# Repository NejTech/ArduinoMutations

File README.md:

Arduino Mutations
============

Here is the resting place of various mutations of Arduino with different MCU's that
I made mostly in 2011 and I decided to release this to the world for reference.
All of the schematic and board designs in this repository are intended to be Open
Source Hardware (OSHW) and are licensed under the Modified BSD License. A short
readme is included in the <name>.txt files.

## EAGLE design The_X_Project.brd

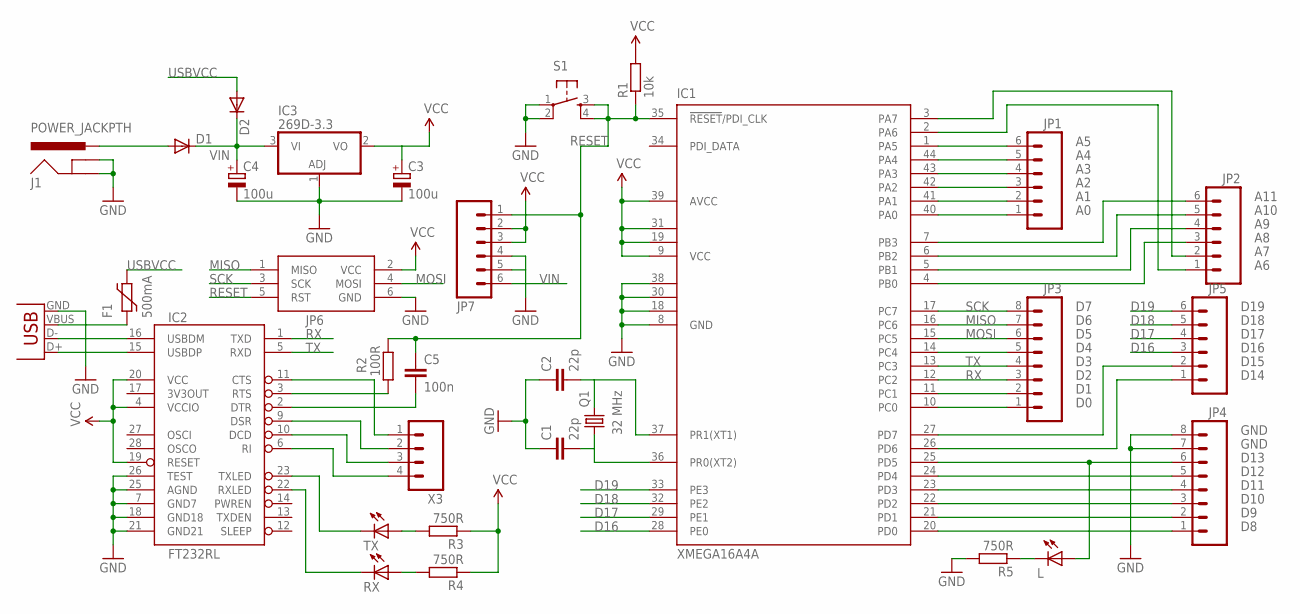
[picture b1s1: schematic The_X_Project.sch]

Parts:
C1, C2: 22p; C0805
C3, C4: 100u; PANASONIC_D
C5: 100n; C0805
D1, D2: DIODE-SMB; SMB
F1: 500mA; 1812L
IC1: XMEGA16A4A; TQFP44
IC2: FT232RL; SSOP28DB
IC3: 269D-3.3; DPACK
J1: POWER_JACKPTH; POWER_JACK_PTH
JP1, JP2, JP5, JP7: M06SIP; 1X06
JP3, JP4: M08; 1X08
JP6: AVRISP-6; AVRISP
L: LED1206; LED-1206
Q1: 32 MHz; HC49U-LM
R1: 10k; R0805
R2: 100R; R0805
R3, R4, R5: 750R; R0805
RX: LED1206; LED-1206
S1: TAC_SWITCHPTH; TACTILE-PTH
TX: LED1206; LED-1206
X1: USBSMD; USB-MINIB
X3: M04PTH; 1X04

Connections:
D16: IC1.28 (PE0), JP5.3
D17: IC1.29 (PE1), JP5.4
D18: IC1.32 (PE2), JP5.5
D19: IC1.33 (PE3), JP5.6
GND: C1.1, C2.1, C3.-, C4.-, IC1.8 (GND), IC1.18 (GND1), IC1.30 (GND2), IC1.38 (GND3), IC2.7 (GND7), IC2.18 (GND18), IC2.21 (GND21), IC2.25 (AGND), IC2.26 (TEST), IC3.1 (ADJ), J1.GND, J1.GNDBREAK, JP4.7, JP4.8, JP6.6 (GND), JP7.4, JP7.5, R5.2, S1.1, S1.2, X1.GND
MISO: IC1.16 (PC6), JP3.7, JP6.1 (MISO)
MOSI: IC1.15 (PC5), JP3.6, JP6.4 (MOSI)
unnamed: IC1.4 (PB0), JP2.3
unnamed: IC1.41 (PA1), JP1.2
unnamed: IC1.42 (PA2), JP1.3
unnamed: IC1.43 (PA3), JP1.4
unnamed: IC1.44 (PA4), JP1.5
unnamed: IC1.1 (PA5), JP1.6
unnamed: IC1.2 (PA6), JP2.1
unnamed: IC1.3 (PA7), JP2.2
unnamed: IC1.5 (PB1), JP2.4
unnamed: IC1.6 (PB2), JP2.5
unnamed: IC1.7 (PB3), JP2.6
unnamed: IC1.10 (PC0), JP3.1
unnamed: IC1.11 (PC1), JP3.2
unnamed: IC2.15 (USBDP), X1.D+
unnamed: IC2.16 (USBDM), X1.D-
unnamed: IC1.14 (PC4), JP3.5
unnamed: IC1.20 (PD0), JP4.1
unnamed: IC1.21 (PD1), JP4.2
unnamed: IC1.22 (PD2), JP4.3
unnamed: IC1.23 (PD3), JP4.4
unnamed: IC1.24 (PD4), JP4.5
unnamed: IC1.25 (PD5), JP4.6, L.A
unnamed: IC1.26 (PD6), JP5.1
unnamed: IC1.27 (PD7), JP5.2
unnamed: IC1.40 (PA0), JP1.1
unnamed: D1.A, J1.PWR
unnamed: F1.P$1 (1), X1.VBUS
unnamed: C1.2, IC1.36 (PR0(XT2)), Q1.1
unnamed: C2.2, IC1.37 (PR1(XT1)), Q1.2
unnamed: IC2.3 (RTS), R2.1
unnamed: C5.2, IC2.2 (DTR)
unnamed: IC2.6 (RI), X3.4
unnamed: IC2.10 (DCD), X3.3
unnamed: IC2.9 (DSR), X3.2
unnamed: IC2.11 (CTS), X3.1
unnamed: IC2.22 (RXLED), RX.C
unnamed: IC2.23 (TXLED), TX.C
unnamed: R4.2, RX.A
unnamed: R3.2, TX.A
unnamed: L.C, R5.1
RESET: C5.1, IC1.35 (!RESET!/PDI_CLK), JP6.5 (RST), JP7.1, R1.1, R2.2, S1.3, S1.4
RX: IC1.12 (PC2), IC2.1 (TXD), JP3.3
SCK: IC1.17 (PC7), JP3.8, JP6.3 (SCK)
TX: IC1.13 (PC3), IC2.5 (RXD), JP3.4
USBVCC: D2.A, F1.P$2 (2)
VCC: C3.+, IC1.9 (VCC), IC1.19 (VCC1), IC1.31 (VCC2), IC1.39 (AVCC), IC2.4 (VCCIO), IC2.19 (RESET), IC2.20 (VCC), IC3.2 (VO), JP6.2 (VCC), JP7.2, JP7.3, R1.2, R3.1, R4.1
VIN: C4.+, D1.C, D2.C, IC3.3 (VI), JP7.6

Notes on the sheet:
A10
A11
D10
D11
D12
D13
GND
D14
D15
D16
D17
D18
D19

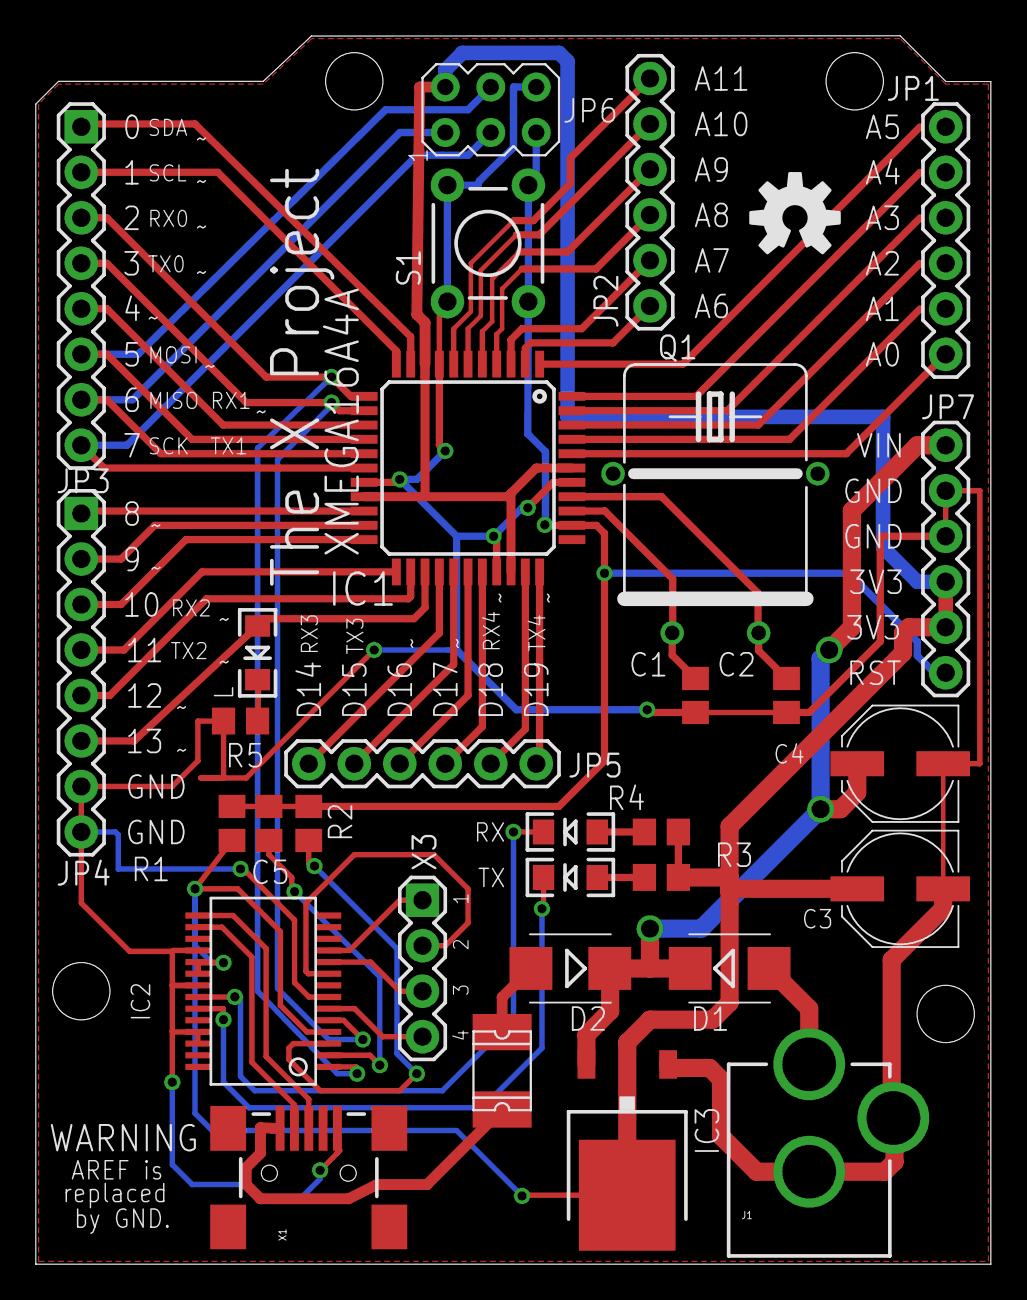
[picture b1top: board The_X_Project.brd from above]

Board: 2 copper layers, 53.3 x 68.6 mm, 32 parts (0 on the bottom side), 54 nets.

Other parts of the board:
U$1: OSHW-LOGO-M

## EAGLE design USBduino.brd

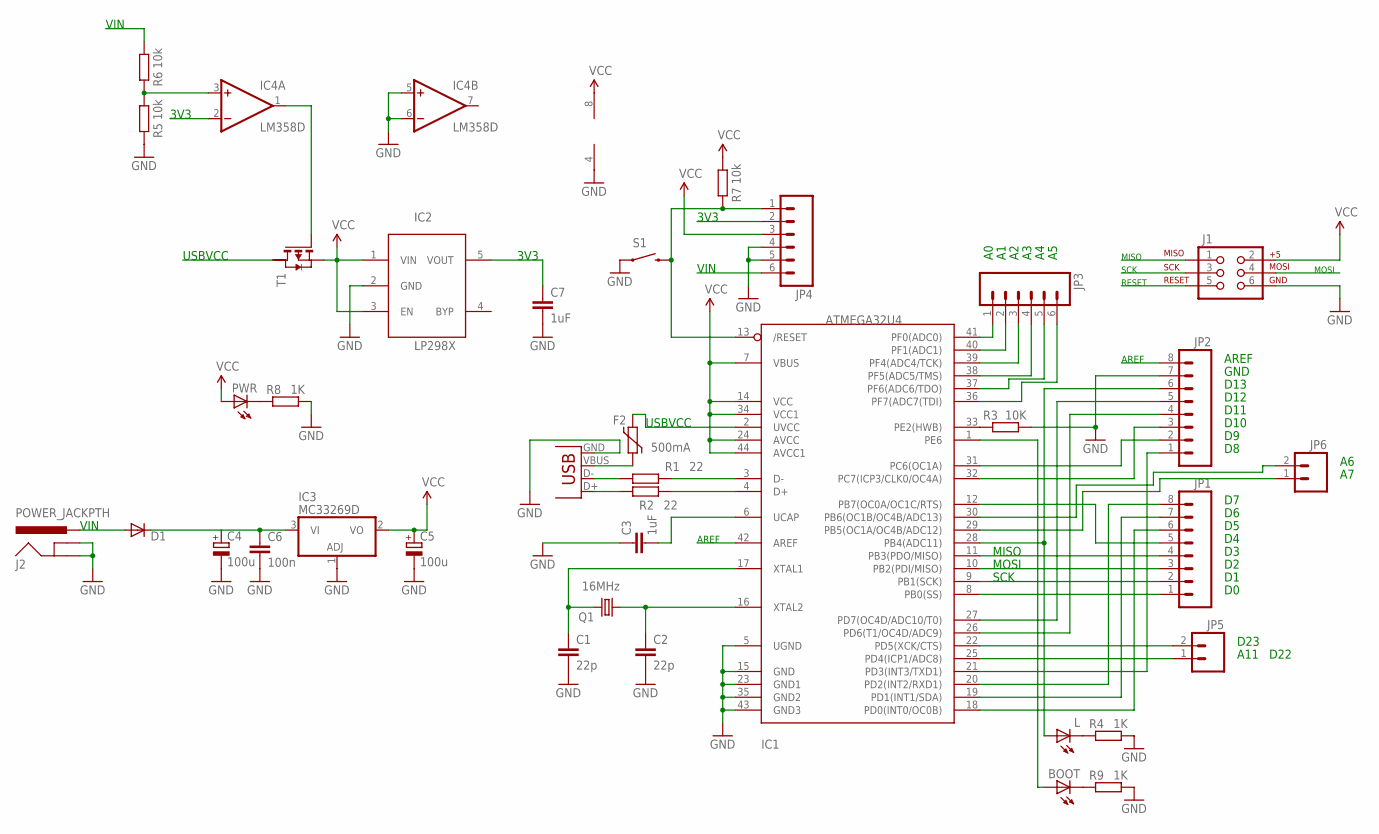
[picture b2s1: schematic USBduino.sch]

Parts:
BOOT: LED1206; LED-1206
C1, C2: 22p; C1206
C3, C7: 1uF; C1206
C4, C5: 100u; UD-6,3X5,8_NICHICON
C6: 100n; C1206
D1: DIODESMA; SMA-DIODE
F2: 500mA; 1812L
IC1: ATMEGA32U4; TQFP44
IC2: LP2985; SOT23-5L
IC3: MC33269D; DPACK
IC4: LM358D; SO08
J1: AVR_SPI_PRG_6NS; 2X3-NS
J2: POWER_JACKPTH; POWER_JACK_PTH
JP1, JP2: M08; 1X08
JP3, JP4: M06SIP; 1X06
JP5, JP6: M02PTH; 1X02
L: LED1206; LED-1206
PWR: LED1206; LED-1206
Q1: 16MHz; HC49/S
R1, R2: 22; R1206
R3: 10K; R1206
R4, R8, R9: 1K; R1206
R5, R6, R7: 10k; R1206
S1: SWITCH-MOMENTARY-2PTH; TACTILE-PTH
T1: PMOSSOT223; SOT223
X1: USBSMD; USB-MINIB

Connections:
3V3: C7.1, IC2.5 (VOUT), IC4.2 (-IN), JP4.2
AREF: IC1.42 (AREF), JP2.8
GND: C1.2, C2.2, C3.1, C4.-, C5.-, C6.2, C7.2, IC1.5 (UGND), IC1.15 (GND), IC1.23 (GND1), IC1.35 (GND2), IC1.43 (GND3), IC2.2 (GND), IC3.1 (ADJ), IC4.4 (V-), IC4.5 (+IN), IC4.6 (-IN), J1.6, J2.GND, J2.GNDBREAK, JP2.7, JP4.4, JP4.5, R3.2, R4.2, R5.1, R8.2, R9.2, S1.1, X1.GND
MISO: IC1.11 (PB3(PDO/MISO)), J1.1, JP1.4
MOSI: IC1.10 (PB2(PDI/MISO)), J1.4, JP1.3
unnamed: IC1.3 (D-), R1.2
unnamed: IC1.4 (D+), R2.2
unnamed: R1.1, X1.D-
unnamed: R2.1, X1.D+
unnamed: C1.1, IC1.17 (XTAL1), Q1.2
unnamed: C2.1, IC1.16 (XTAL2), Q1.1
unnamed: IC1.8 (PB0(SS)), JP1.1
unnamed: IC1.33 (PE2(HWB)), R3.1
unnamed: L.C, R4.1
unnamed: IC1.25 (PD4(ICP1/ADC8)), JP5.1
unnamed: IC1.12 (PB7(OC0A/OC1C/RTS)), JP1.5
unnamed: IC1.18 (PD0(INT0/OC0B)), JP1.6
unnamed: IC1.19 (PD1(INT1/SDA)), JP1.7
unnamed: IC1.20 (PD2(INT2/RXD1)), JP1.8
unnamed: IC1.21 (PD3(INT3/TXD1)), JP2.1
unnamed: IC1.31 (PC6(OC1A)), JP2.2
unnamed: IC1.32 (PC7(ICP3/CLK0/OC4A)), JP2.3
unnamed: IC1.26 (PD6(T1/OC4D/ADC9)), JP2.4
unnamed: IC1.27 (PD7(OC4D/ADC10/T0)), JP2.5
unnamed: IC1.28 (PB4(ADC11)), JP2.6, L.A
unnamed: IC1.41 (PF0(ADC0)), JP3.1
unnamed: IC1.40 (PF1(ADC1)), JP3.2
unnamed: IC1.39 (PF4(ADC4/TCK)), JP3.3
unnamed: IC1.38 (PF5(ADC5/TMS)), JP3.4
unnamed: IC1.37 (PF6(ADC6/TDO)), JP3.5
unnamed: IC1.36 (PF7(ADC7(TDI)), JP3.6
unnamed: C3.2, IC1.6 (UCAP)
unnamed: IC4.1 (OUT), T1.1 (G)
unnamed: IC1.22 (PD5(XCK/CTS)), JP5.2
unnamed: IC4.3 (+IN), R5.2, R6.1
unnamed: C4.+, C6.1, D1.C, IC3.3 (VI)
unnamed: F2.P$1 (1), X1.VBUS
unnamed: PWR.C, R8.1
unnamed: IC1.29 (PB5(OC1A/OC4B/ADC12)), JP6.1
unnamed: IC1.30 (PB6(OC1B/OC4B/ADC13)), JP6.2
unnamed: BOOT.C, R9.1
unnamed: BOOT.A, IC1.1 (PE6)
RESET: IC1.13 (/RESET), J1.5, JP4.1, R7.1, S1.3 (2)
SCK: IC1.9 (PB1(SCK)), J1.3, JP1.2
USBVCC: F2.P$2 (2), IC1.2 (UVCC), T1.2 (D)
VCC: C5.+, IC1.7 (VBUS), IC1.14 (VCC), IC1.24 (AVCC), IC1.34 (VCC1), IC1.44 (AVCC1), IC2.1 (VIN), IC2.3 (EN), IC3.2 (VO), IC4.8 (V+), J1.2, JP4.3, PWR.A, R7.2, T1.3 (S)
VIN: D1.A, J2.PWR, JP4.6, R6.2

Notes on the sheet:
AREF
D10
D11
D12
D13
GND
MOSI
SCK
RESET
MISO
VIN
3V3
USBVCC
A11
D23
D22

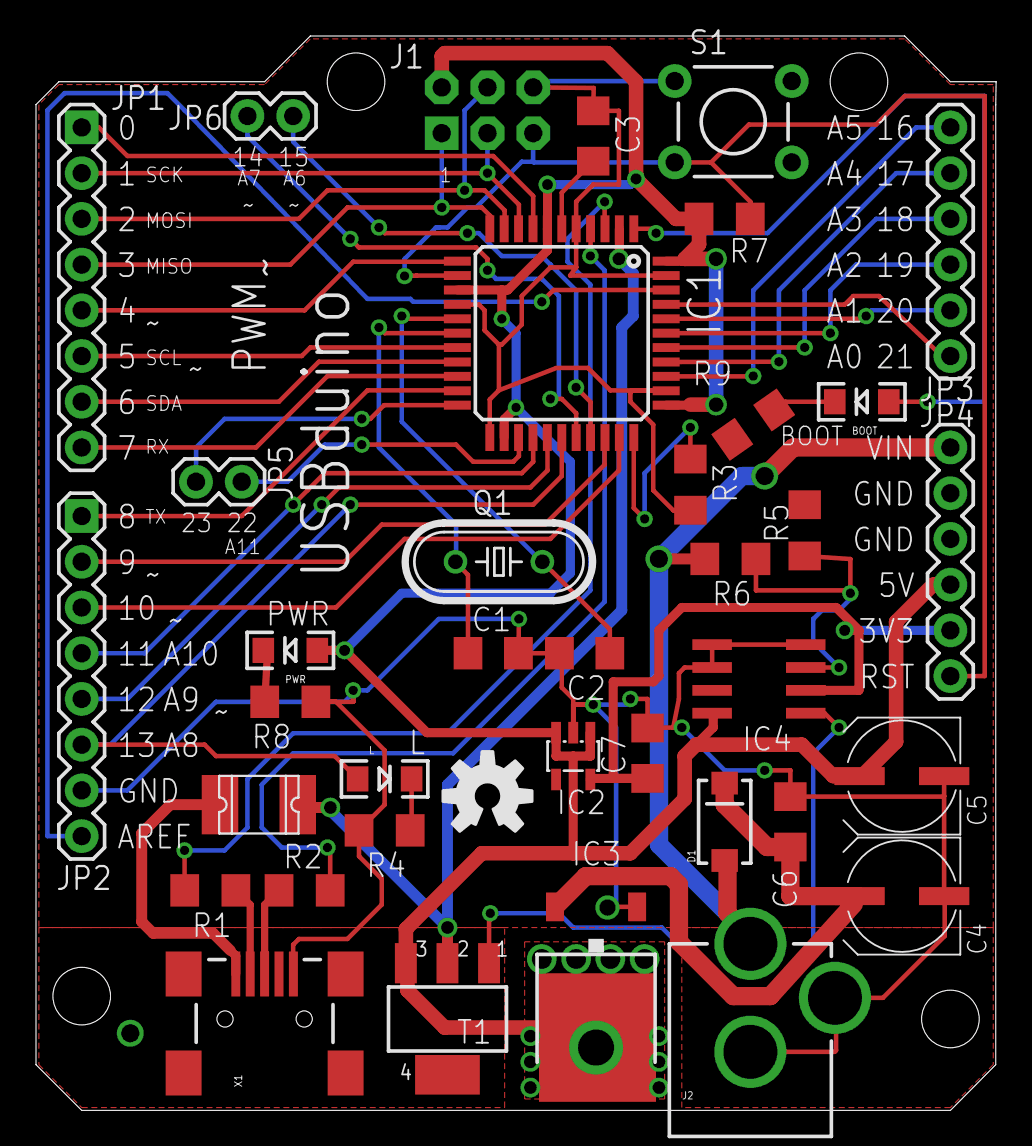
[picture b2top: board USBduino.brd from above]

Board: 2 copper layers, 53.3 x 59.7 mm, 38 parts (0 on the bottom side), 47 nets.

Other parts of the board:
U$2: OSHW-LOGO-M

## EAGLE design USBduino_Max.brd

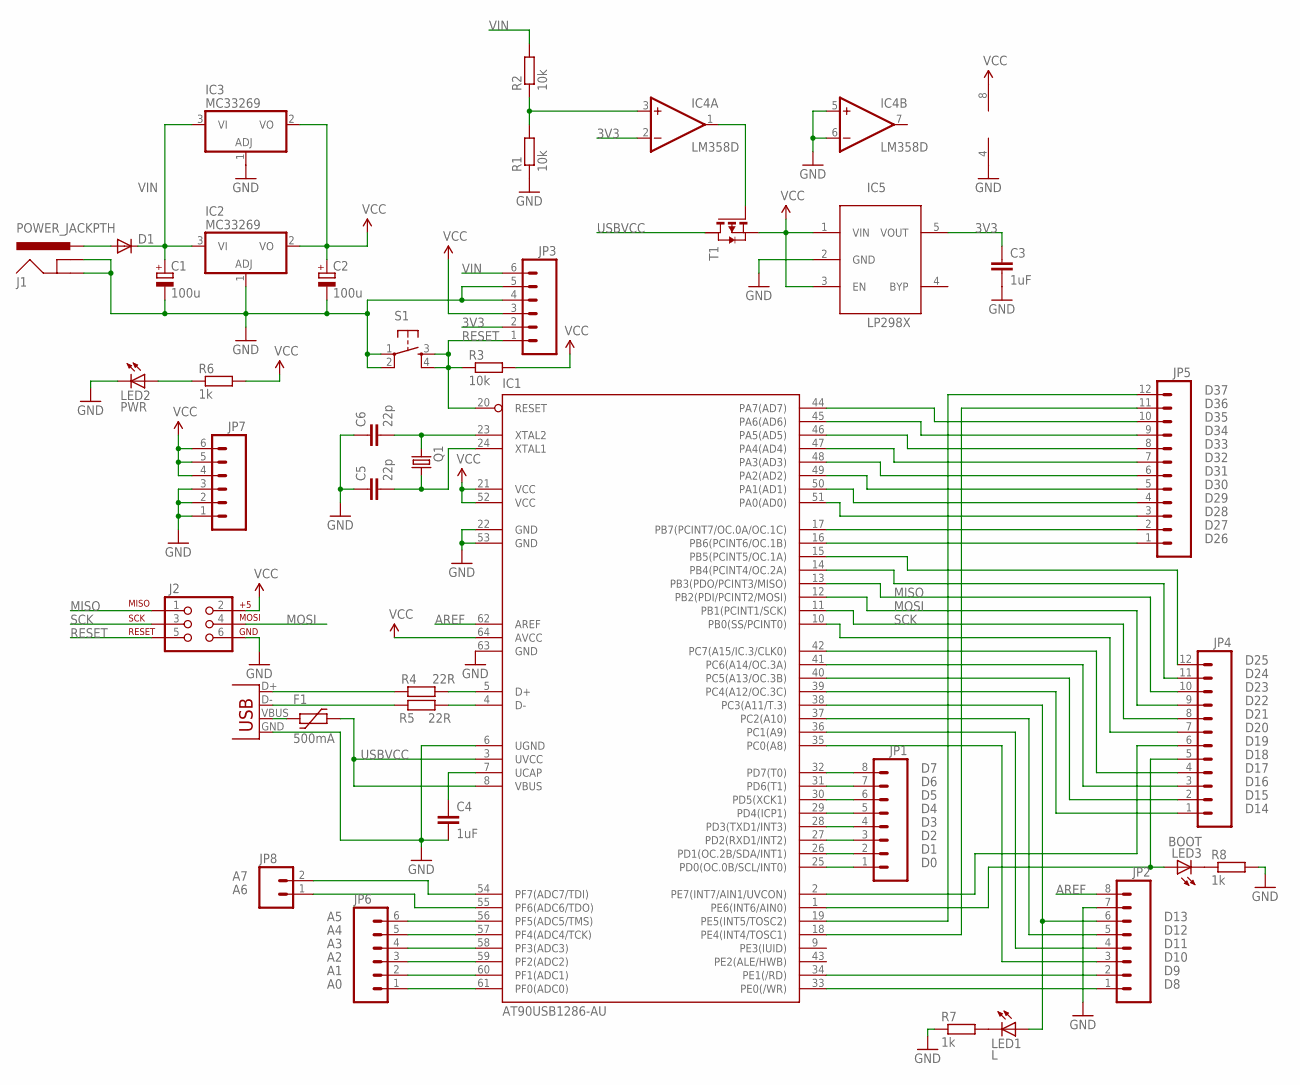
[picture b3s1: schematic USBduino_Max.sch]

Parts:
C1, C2: 100u; PANASONIC_C
C3, C4: 1uF; C0805
C5, C6: 22p; C0805
D1: DIODE-SMB; SMB
F1: 500mA; 1812L
IC1: AT90USB1286-AU; TQFP64
IC2, IC3: MC33269; DPACK
IC4: LM358D; SO08
IC5: LP2985; SOT23-5L
J1: POWER_JACKPTH; POWER_JACK_PTH
J2: AVR_SPI_PRG_6PTH; 2X3
JP1, JP2: M08; 1X08
JP3, JP6, JP7: M06SIP; 1X06
JP4, JP5: M12PTH; 1X12
JP8: M02PTH; 1X02
LED1: L; LED-1206
LED2: PWR; LED-1206
LED3: BOOT; LED-1206
Q1: CRYSTALHC49S; HC49/S
R1, R2, R3: 10k; R0805
R4, R5: 22R; R0805
R6, R7, R8: 1k; R0805
S1: TAC_SWITCHPTH; TACTILE-PTH
T1: PMOSSOT223; SOT223
X1: USBPTH; USB-B-PTH

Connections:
3V3: C3.1, IC4.2 (-IN), IC5.5 (VOUT), JP3.2
AREF: IC1.62 (AREF), JP2.8
GND: C1.-, C2.-, C3.2, C4.2, C5.1, C6.1, IC1.6 (UGND), IC1.22 (GND), IC1.53 (GND), IC1.63 (GND), IC2.1 (ADJ), IC3.1 (ADJ), IC4.4 (V-), IC4.5 (+IN), IC4.6 (-IN), IC5.2 (GND), J1.GND, J1.GNDBREAK, J2.6, JP2.7, JP3.4, JP3.5, JP7.1, JP7.2, JP7.3, LED2.C, R1.1, R7.1, R8.2, S1.1, S1.2, X1.GND
MISO: IC1.13 (PB3(PDO/PCINT3/MISO)), J2.1, JP4.10
MOSI: IC1.12 (PB2(PDI/PCINT2/MOSI)), J2.4, JP4.9
unnamed: IC4.3 (+IN), R1.2, R2.1
unnamed: D1.A, J1.PWR
unnamed: IC4.1 (OUT), T1.1 (G)
unnamed: IC1.25 (PD0(OC.0B/SCL/INT0)), JP1.1
unnamed: IC1.26 (PD1(OC.2B/SDA/INT1)), JP1.2
unnamed: IC1.27 (PD2(RXD1/INT2)), JP1.3
unnamed: IC1.28 (PD3(TXD1/INT3)), JP1.4
unnamed: IC1.29 (PD4(ICP1)), JP1.5
unnamed: IC1.30 (PD5(XCK1)), JP1.6
unnamed: IC1.31 (PD6(T1)), JP1.7
unnamed: IC1.32 (PD7(T0)), JP1.8
unnamed: IC1.33 (PE0(/WR)), JP2.1
unnamed: IC1.34 (PE1(/RD)), JP2.2
unnamed: IC1.35 (PC0(A8)), JP2.3
unnamed: IC1.36 (PC1(A9)), JP2.4
unnamed: IC1.37 (PC2(A10)), JP2.5
unnamed: IC1.38 (PC3(A11/T.3)), JP2.6, LED1.A
unnamed: IC1.5 (D+), R4.2
unnamed: IC1.4 (D-), R5.2
unnamed: R5.1, X1.D-
unnamed: R4.1, X1.D+
unnamed: C6.2, IC1.23 (XTAL2), Q1.2
unnamed: C4.1, IC1.7 (UCAP)
unnamed: C5.2, IC1.24 (XTAL1), Q1.1
unnamed: F1.P$1 (1), X1.VBUS
unnamed: IC1.39 (PC4(A12/OC.3C)), JP4.1
unnamed: IC1.40 (PC5(A13/OC.3B)), JP4.2
unnamed: IC1.41 (PC6(A14/OC.3A)), JP4.3
unnamed: IC1.42 (PC7(A15/IC.3/CLK0)), JP4.4
unnamed: IC1.1 (PE6(INT6/AIN0)), JP4.5, LED3.A
unnamed: IC1.2 (PE7(INT7/AIN1/UVCON)), JP4.6
unnamed: IC1.10 (PB0(SS/PCINT0)), JP4.7
unnamed: LED2.A, R6.1
unnamed: LED1.C, R7.2
unnamed: LED3.C, R8.1
unnamed: IC1.14 (PB4(PCINT4/OC.2A)), JP4.11
unnamed: IC1.15 (PB5(PCINT5/OC.1A)), JP4.12
unnamed: IC1.16 (PB6(PCINT6/OC.1B)), JP5.1
unnamed: IC1.17 (PB7(PCINT7/OC.0A/OC.1C)), JP5.2
unnamed: IC1.51 (PA0(AD0)), JP5.3
unnamed: IC1.50 (PA1(AD1)), JP5.4
unnamed: IC1.49 (PA2(AD2)), JP5.5
unnamed: IC1.48 (PA3(AD3)), JP5.6
unnamed: IC1.47 (PA4(AD4)), JP5.7
unnamed: IC1.46 (PA5(AD5)), JP5.8
unnamed: IC1.45 (PA6(AD6)), JP5.9
unnamed: IC1.44 (PA7(AD7)), JP5.10
unnamed: IC1.18 (PE4(INT4/TOSC1)), JP5.11
unnamed: IC1.19 (PE5(INT5/TOSC2)), JP5.12
unnamed: IC1.61 (PF0(ADC0)), JP6.1
unnamed: IC1.60 (PF1(ADC1)), JP6.2
unnamed: IC1.59 (PF2(ADC2)), JP6.3
unnamed: IC1.58 (PF3(ADC3)), JP6.4
unnamed: IC1.57 (PF4(ADC4/TCK)), JP6.5
unnamed: IC1.56 (PF5(ADC5/TMS)), JP6.6
unnamed: IC1.55 (PF6(ADC6/TDO)), JP8.1
unnamed: IC1.54 (PF7(ADC7/TDI)), JP8.2
RESET: IC1.20 (RESET), J2.5, JP3.1, R3.1, S1.3, S1.4
SCK: IC1.11 (PB1(PCINT1/SCK)), J2.3, JP4.8
USBVCC: F1.P$2 (2), IC1.3 (UVCC), IC1.8 (VBUS), T1.2 (D)
VCC: C2.+, IC1.21 (VCC), IC1.52 (VCC), IC1.64 (AVCC), IC2.2 (VO), IC3.2 (VO), IC4.8 (V+), IC5.1 (VIN), IC5.3 (EN), J2.2, JP3.3, JP7.4, JP7.5, JP7.6, R3.2, R6.2, T1.3 (S)
VIN: C1.+, D1.C, IC2.3 (VI), IC3.3 (VI), JP3.6, R2.2

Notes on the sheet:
D10
D11
D12
D13
D14
D15
D16
D17
D18
D19
D20
D21
D22
D23
D24
D25
D26
D27
D28
D29
D30
D31
D32
D33
D34
D35
D36
D37

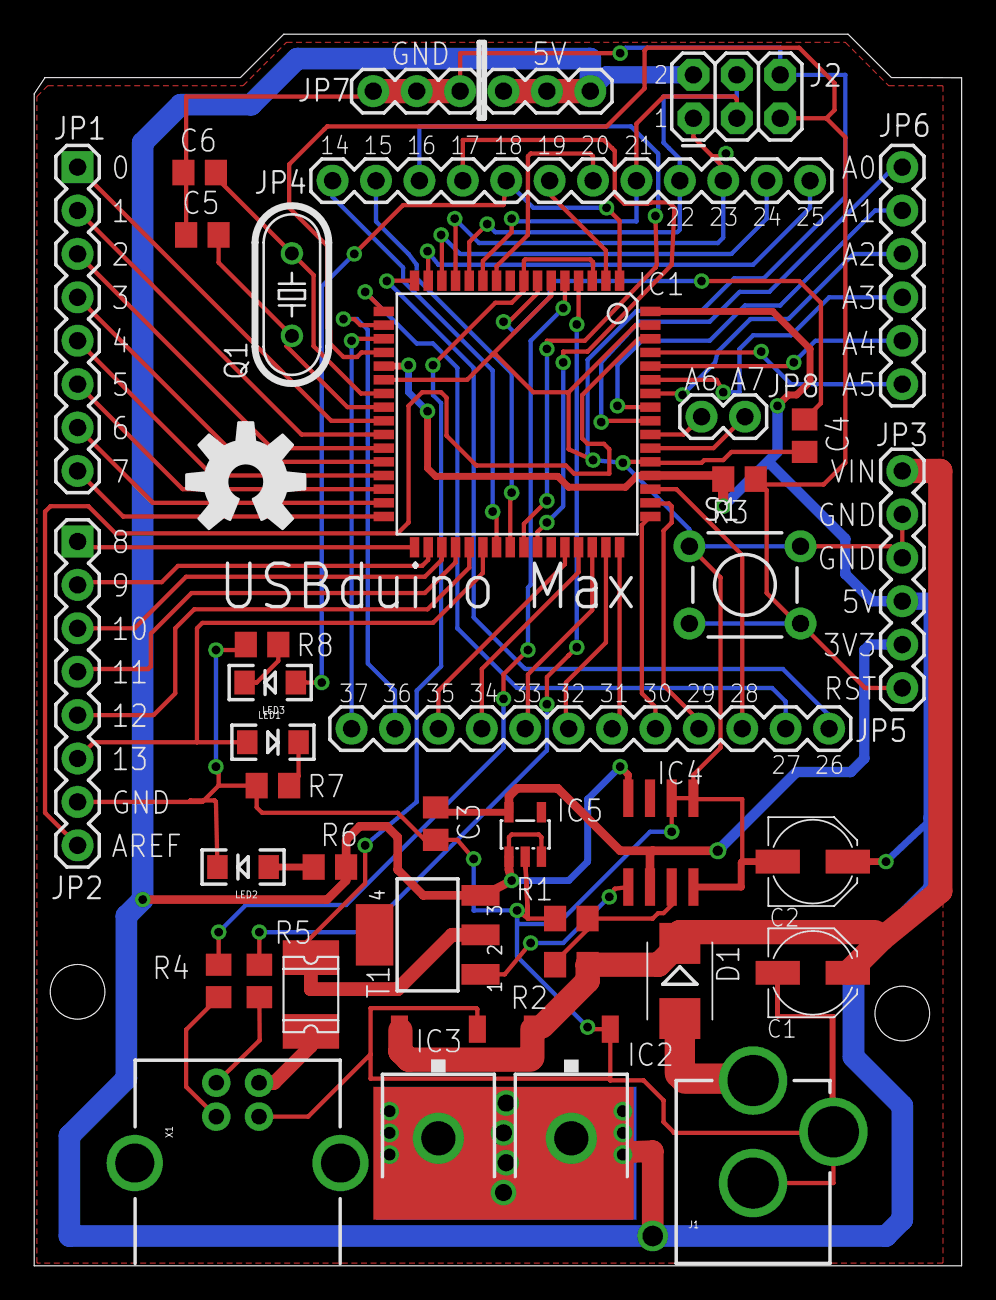
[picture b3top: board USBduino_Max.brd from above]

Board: 2 copper layers, 54.3 x 72.1 mm, 39 parts (0 on the bottom side), 67 nets.

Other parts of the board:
U$1: OSHW-LOGO-L

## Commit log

2013-07-11 Initial upload of the good stuff.
2013-07-11 Forgot one little part of the USBduino Max readme, fixing it.

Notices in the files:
parts and their libraries:
SparkFun-Aesthetics: Licensing: CC v3.0 Share-Alike You are welcome to use this library for commercial purposes.
